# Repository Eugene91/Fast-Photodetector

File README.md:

# Fast-Photodetector
Kicad design of high speed photodetector (~200 MHz) that is based on OPA 857 Transimpedance circuit. 
## Few notes:
- Circuit is designed and tested with Hamamatsu [Hamamatsu S5972](https://www.hamamatsu.com/eu/en/product/type/S5972/index.html) photodiodes  but maybe used with other photodiodes with similar or larger capacitance (note that the bandwidth may be photodiode limited in this case). 
- Circuit is supplied by external 9-15V voltage via pin connectors. 
- The datasheet of OPA 857 suggests installing shunting capacitance in parallel with R3 with a capacitance of 0.1 pF. 
However the experiment did not show the much performance difference in the presence of the capacitance.
- The first version of the photodetector is depicted below.

Some changes were introduced in the current version:
- Through hole capacitors are replaced SMD components.
- All passive SMD components are replaced with 1206 case for convenience
- 0.1 pF capacitance is removed.

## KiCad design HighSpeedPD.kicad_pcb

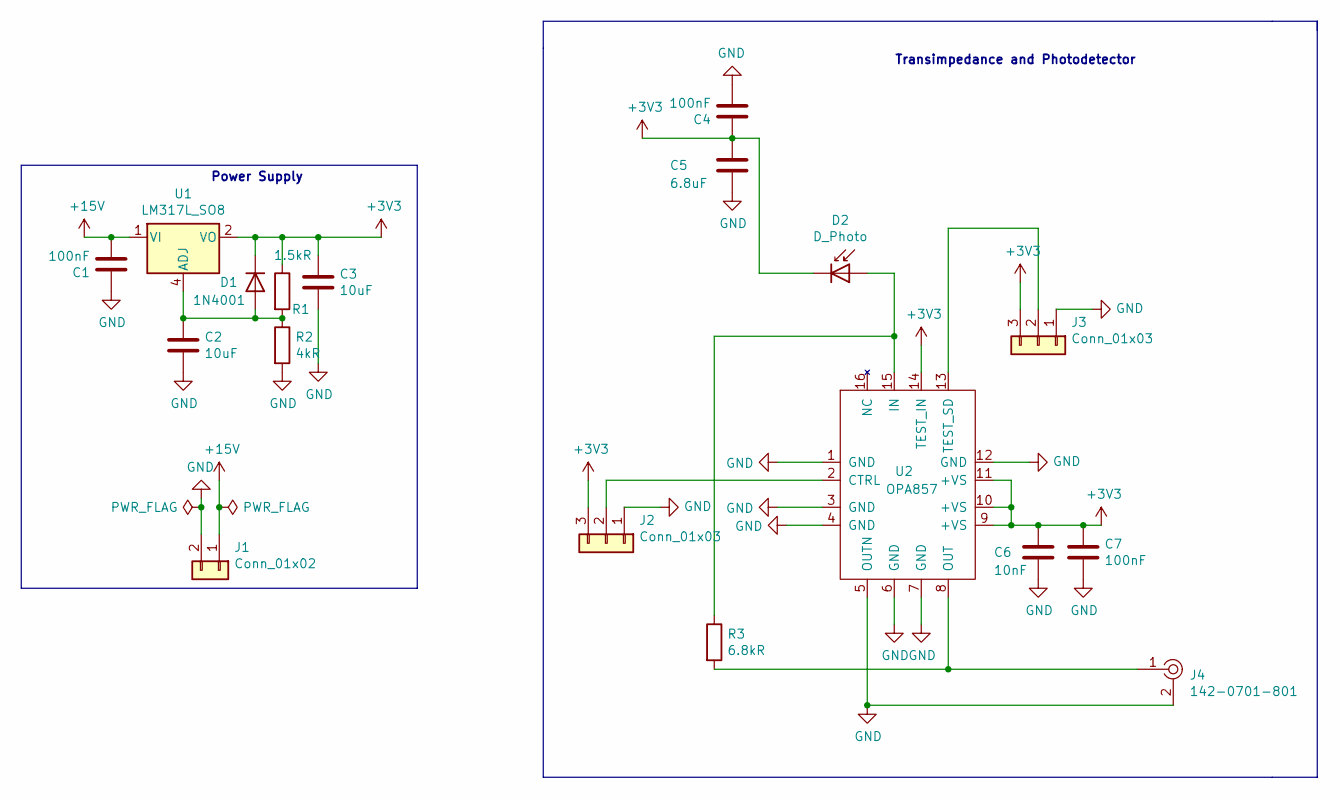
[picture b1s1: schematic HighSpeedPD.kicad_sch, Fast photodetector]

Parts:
C1, C4, C7: 100nF; C_1206_3216Metric
C2, C3: 10uF; C_1206_3216Metric
C5: 6.8uF; C_1206_3216Metric
C6: 10nF; C_1206_3216Metric
D1: 1N4001; D_DO-41_SOD81_P10.16mm_Horizontal
D2: D_Photo; TO-18-3
J1: Conn_01x02; PinHeader_1x02_P2.54mm_Vertical
J2, J3: Conn_01x03; PinHeader_1x03_P2.54mm_Vertical
J4: 142-0701-801; RF_SMA_BoardEdge_142-0701-801; MPN 142-0701-801; Digi-Key_PN J502-ND
R1: 1.5kR; R_1206_3216Metric
R2: 4kR; R_1206_3216Metric
R3: 6.8kR; R_1206_3216Metric
U1: LM317L_SO8; SOIC-8_3.9x4.9mm_P1.27mm
U2: OPA857; VFQFN-16-1EP_3x3mm

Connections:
+3V3: C3.1, C4.1, C5.1, C6.1, C7.1, D1.1 (K), D2.1 (K), J2.3, J3.3, R1.1, U1.2 (VO), U1.3 (VO), U1.6 (VO), U1.7 (VO), U2.9 (+VS), U2.10 (+VS), U2.11 (+VS), U2.14 (TEST_IN)
+15V: C1.2, J1.1, U1.1 (VI)
GND: C1.1, C2.2, C3.2, C4.2, C5.2, C6.2, C7.2, J1.2, J2.1, J3.1, J4.2, R2.2, U2.1 (GND), U2.3 (GND), U2.4 (GND), U2.5 (OUTN), U2.6 (GND), U2.7 (GND), U2.12 (GND)
unnamed: C2.1, D1.2 (A), R1.2, R2.1, U1.4 (ADJ)
unnamed: D2.2 (A), R3.1, U2.15 (IN)
unnamed: J2.2, U2.2 (CTRL)
unnamed: J3.2, U2.13 (TEST_SD)
unnamed: J4.1, R3.2, U2.8 (OUT)

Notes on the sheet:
Transimpedance and Photodetector
Power Supply

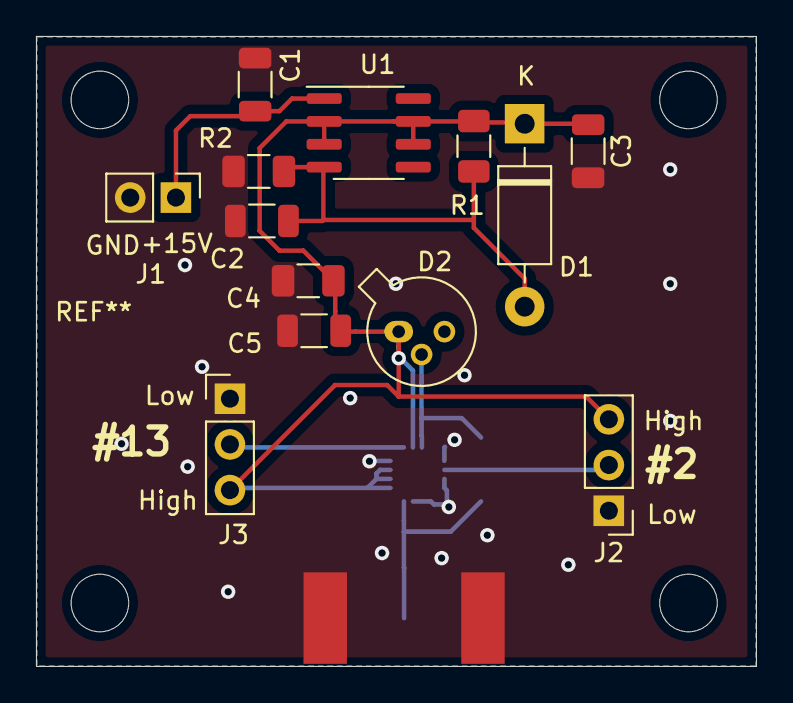
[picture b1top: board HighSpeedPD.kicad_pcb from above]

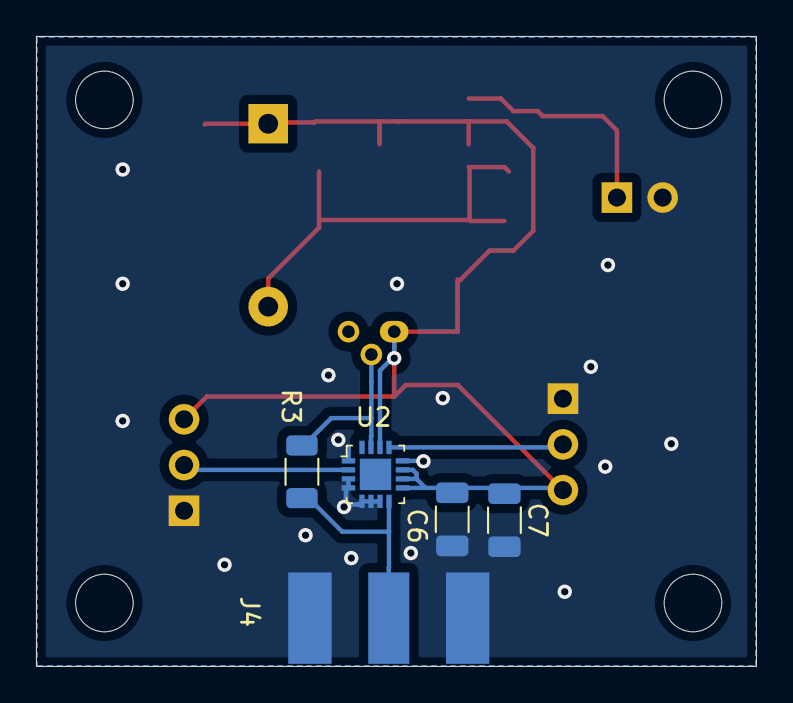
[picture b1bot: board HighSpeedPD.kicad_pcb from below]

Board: 2 copper layers, 40.0 x 35.0 mm, 18 parts (5 on the bottom side), 8 nets.

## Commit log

2023-01-24 small fix
